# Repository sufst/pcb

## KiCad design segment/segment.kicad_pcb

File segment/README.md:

# Segment PCB Info

To comply with isolation requirements for HV and LV, this design has been split
up into two PCBs. The "HV" board provides the fusing and connections for the
voltage taps. The "LV" board provides the connections to the thermistors and
merges their grounds. The boards are designed to be stacked vertically with
the LV board on top of the HV board. The boards should be connected via an 
insulating material and should be separated either by at least 30mm of air
or be separated by a barrier of moisture resistant, insulating material.

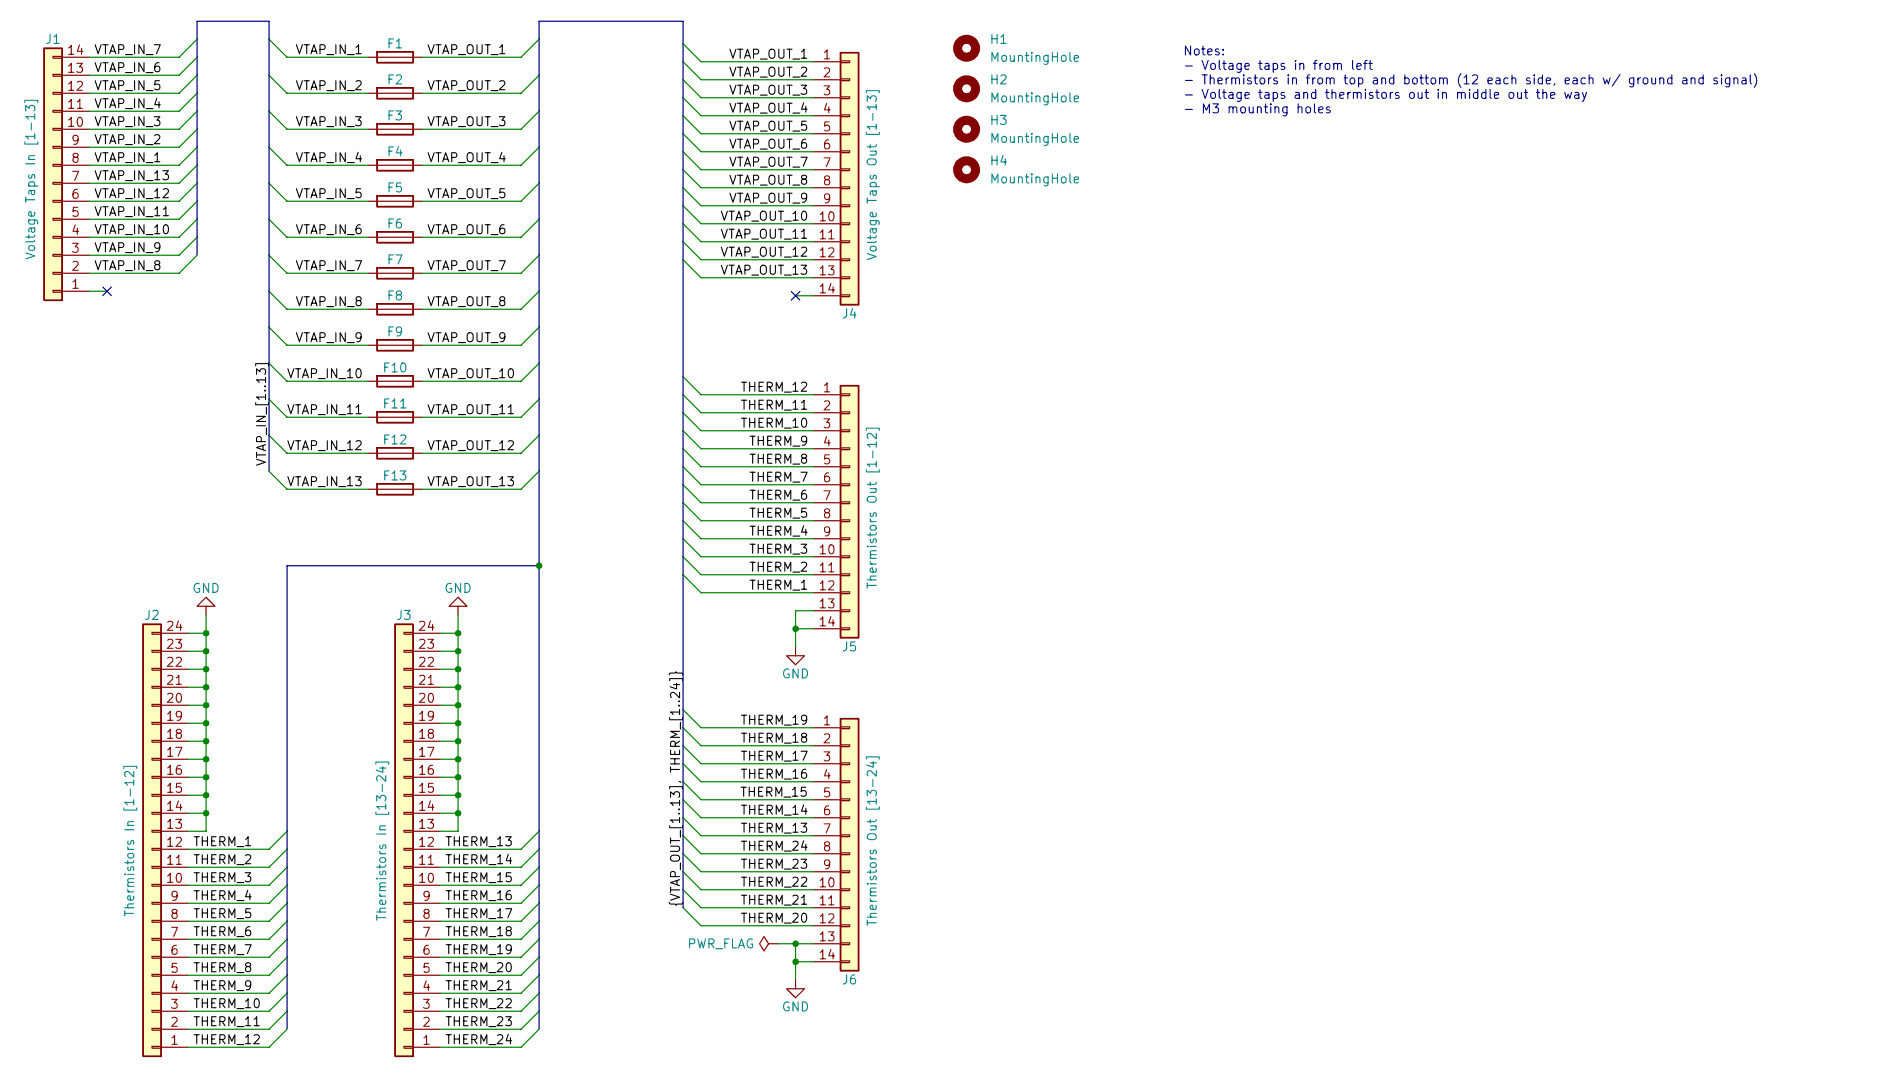
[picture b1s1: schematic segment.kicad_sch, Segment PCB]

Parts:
F1, F2, F3, F4, F5, F6, F7, F8, F9, F10, F11, F12, F13: Fuse; Littelfuse-04611-25ER
H1, H2, H3, H4: MountingHole; MountingHole_4.3mm_M4
J1: Voltage Taps In [1-13]; Molex_Micro-Fit_3.0_43045-1400_2x07_P3.00mm_Horizontal
J2: Thermistors In [1-12]; Molex_Micro-Fit_3.0_43045-2400_2x12_P3.00mm_Horizontal
J3: Thermistors In [13-24]; Molex_Micro-Fit_3.0_43045-2400_2x12_P3.00mm_Horizontal
J4: Voltage Taps Out [1-13]; Molex_Micro-Fit_3.0_43045-1412_2x07_P3.00mm_Vertical
J5: Thermistors Out [1-12]; Molex_Micro-Fit_3.0_43045-1412_2x07_P3.00mm_Vertical
J6: Thermistors Out [13-24]; Molex_Micro-Fit_3.0_43045-1412_2x07_P3.00mm_Vertical

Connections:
/THERM_1: J2.12, J5.12
/THERM_2: J2.11, J5.11
/THERM_3: J2.10, J5.10
/THERM_4: J2.9, J5.9
/THERM_5: J2.8, J5.8
/THERM_6: J2.7, J5.7
/THERM_7: J2.6, J5.6
/THERM_8: J2.5, J5.5
/THERM_9: J2.4, J5.4
/THERM_10: J2.3, J5.3
/THERM_11: J2.2, J5.2
/THERM_12: J2.1, J5.1
/THERM_13: J3.12, J6.7
/THERM_14: J3.11, J6.6
/THERM_15: J3.10, J6.5
/THERM_16: J3.9, J6.4
/THERM_17: J3.8, J6.3
/THERM_18: J3.7, J6.2
/THERM_19: J3.6, J6.1
/THERM_20: J3.5, J6.12
/THERM_21: J3.4, J6.11
/THERM_22: J3.3, J6.10
/THERM_23: J3.2, J6.9
/THERM_24: J3.1, J6.8
/VTAP_IN_1: F1.2, J1.8
/VTAP_IN_2: F2.2, J1.9
/VTAP_IN_3: F3.2, J1.10
/VTAP_IN_4: F4.2, J1.11
/VTAP_IN_5: F5.2, J1.12
/VTAP_IN_6: F6.2, J1.13
/VTAP_IN_7: F7.2, J1.14
/VTAP_IN_8: F8.2, J1.2
/VTAP_IN_9: F9.2, J1.3
/VTAP_IN_10: F10.2, J1.4
/VTAP_IN_11: F11.2, J1.5
/VTAP_IN_12: F12.2, J1.6
/VTAP_IN_13: F13.2, J1.7
/VTAP_OUT_1: F1.1, J4.1
/VTAP_OUT_2: F2.1, J4.2
/VTAP_OUT_3: F3.1, J4.3
/VTAP_OUT_4: F4.1, J4.4
/VTAP_OUT_5: F5.1, J4.5
/VTAP_OUT_6: F6.1, J4.6
/VTAP_OUT_7: F7.1, J4.7
/VTAP_OUT_8: F8.1, J4.8
/VTAP_OUT_9: F9.1, J4.9
/VTAP_OUT_10: F10.1, J4.10
/VTAP_OUT_11: F11.1, J4.11
/VTAP_OUT_12: F12.1, J4.12
/VTAP_OUT_13: F13.1, J4.13
GND: J2.13, J2.14, J2.15, J2.16, J2.17, J2.18, J2.19, J2.20, J2.21, J2.22, J2.23, J2.24, J3.13, J3.14, J3.15, J3.16, J3.17, J3.18, J3.19, J3.20, J3.21, J3.22, J3.23, J3.24, J5.13, J5.14, J6.13, J6.14

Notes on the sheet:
Notes: - Voltage taps in from left - Thermistors in from top and bottom (12 each side, each w/ ground and signal) - Voltage taps and thermistors out in middle out the way - M3 mounting holes

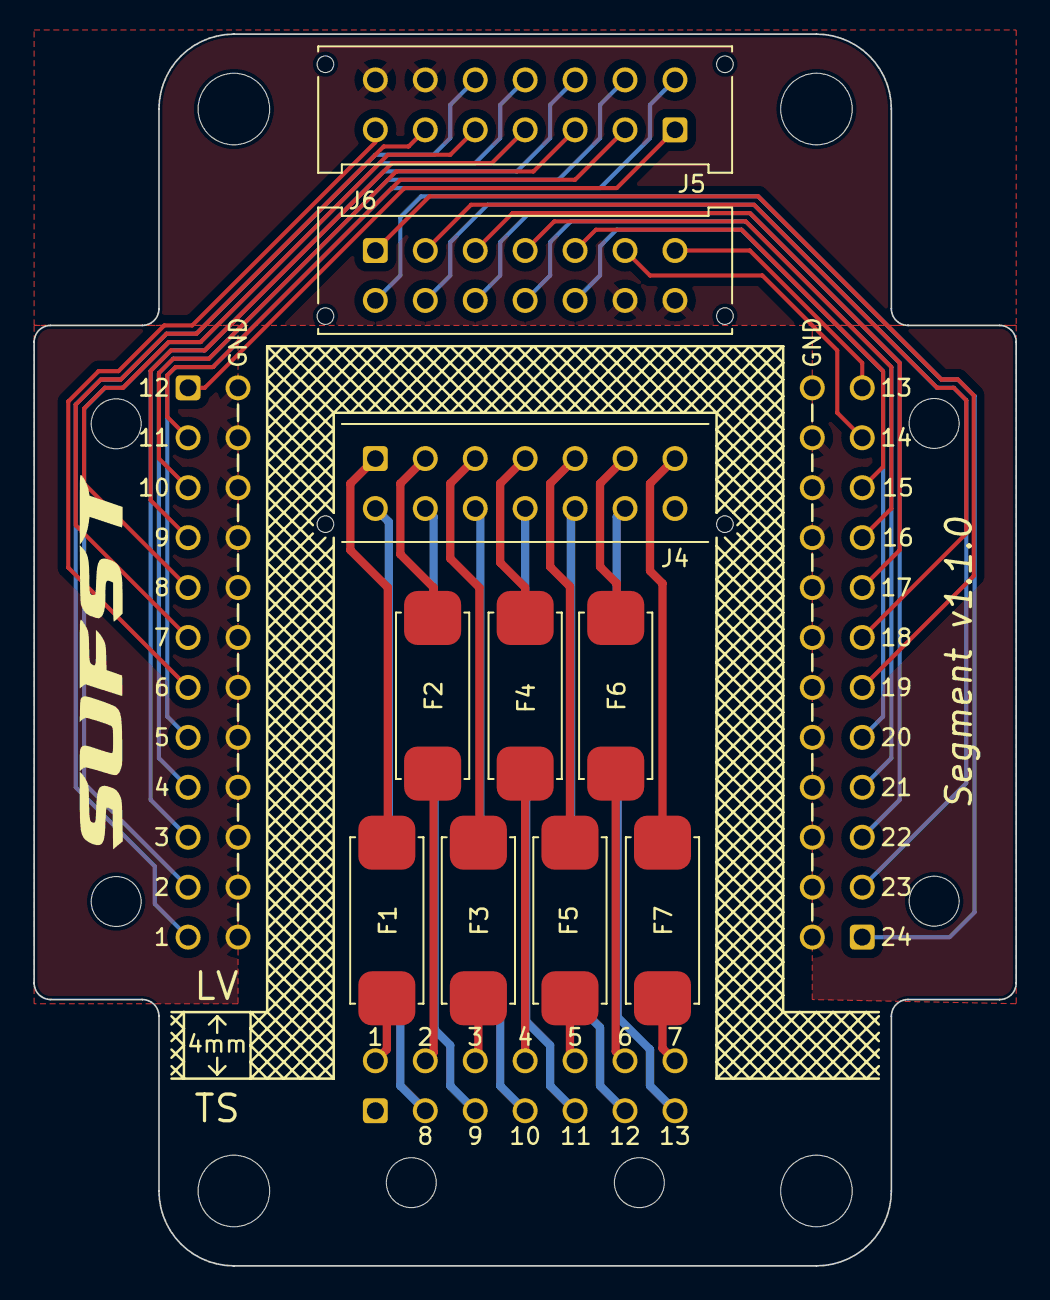
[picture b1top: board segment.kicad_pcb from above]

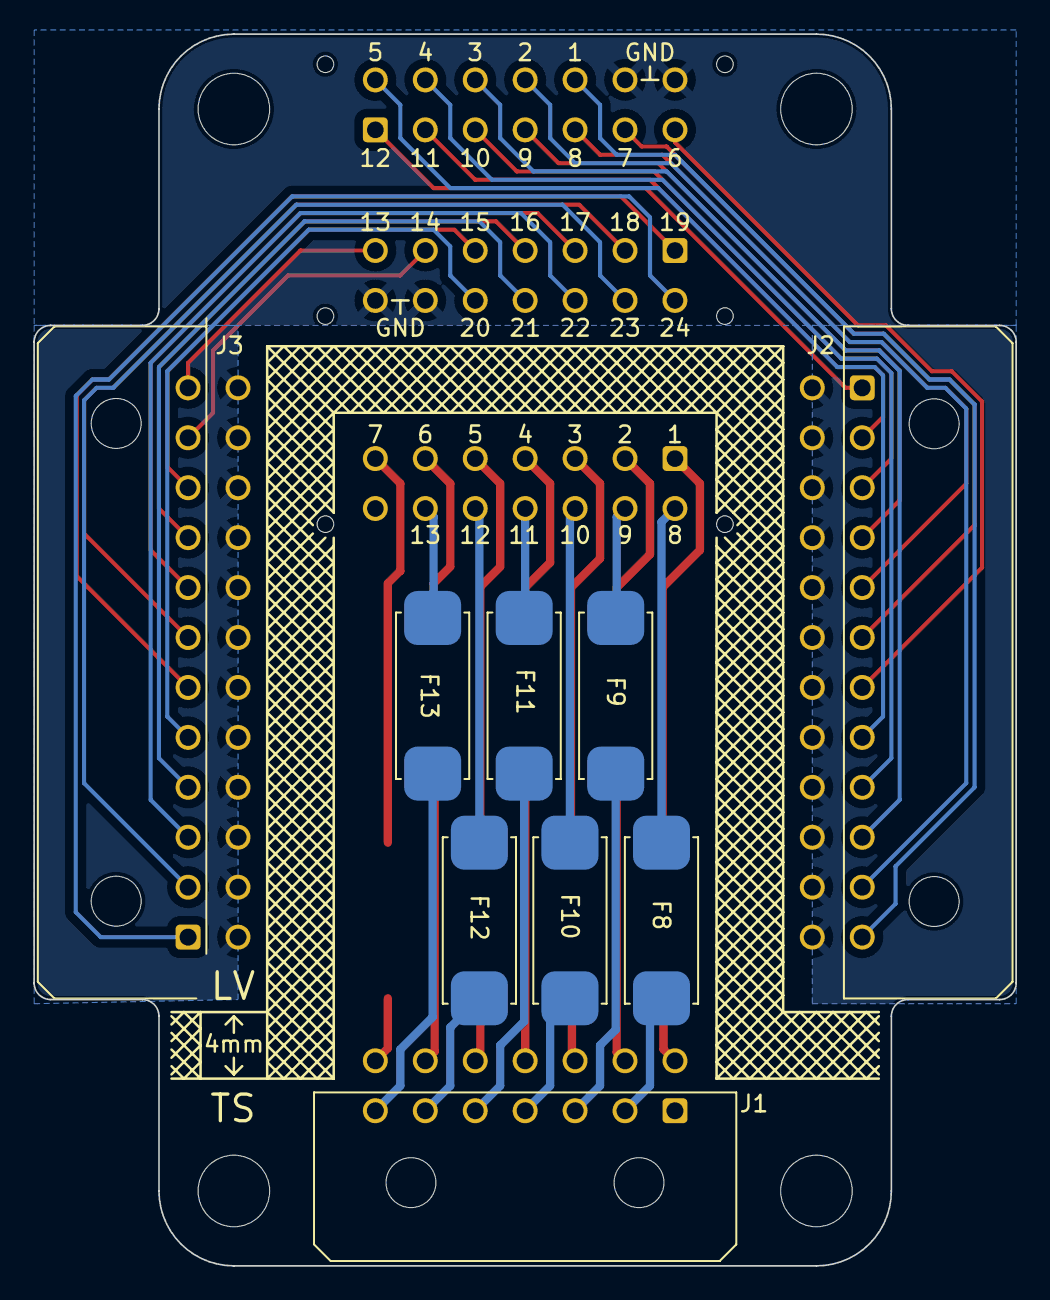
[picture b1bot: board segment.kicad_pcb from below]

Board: 4 copper layers, 59.0 x 74.0 mm, 23 parts (9 on the bottom side), 51 nets.

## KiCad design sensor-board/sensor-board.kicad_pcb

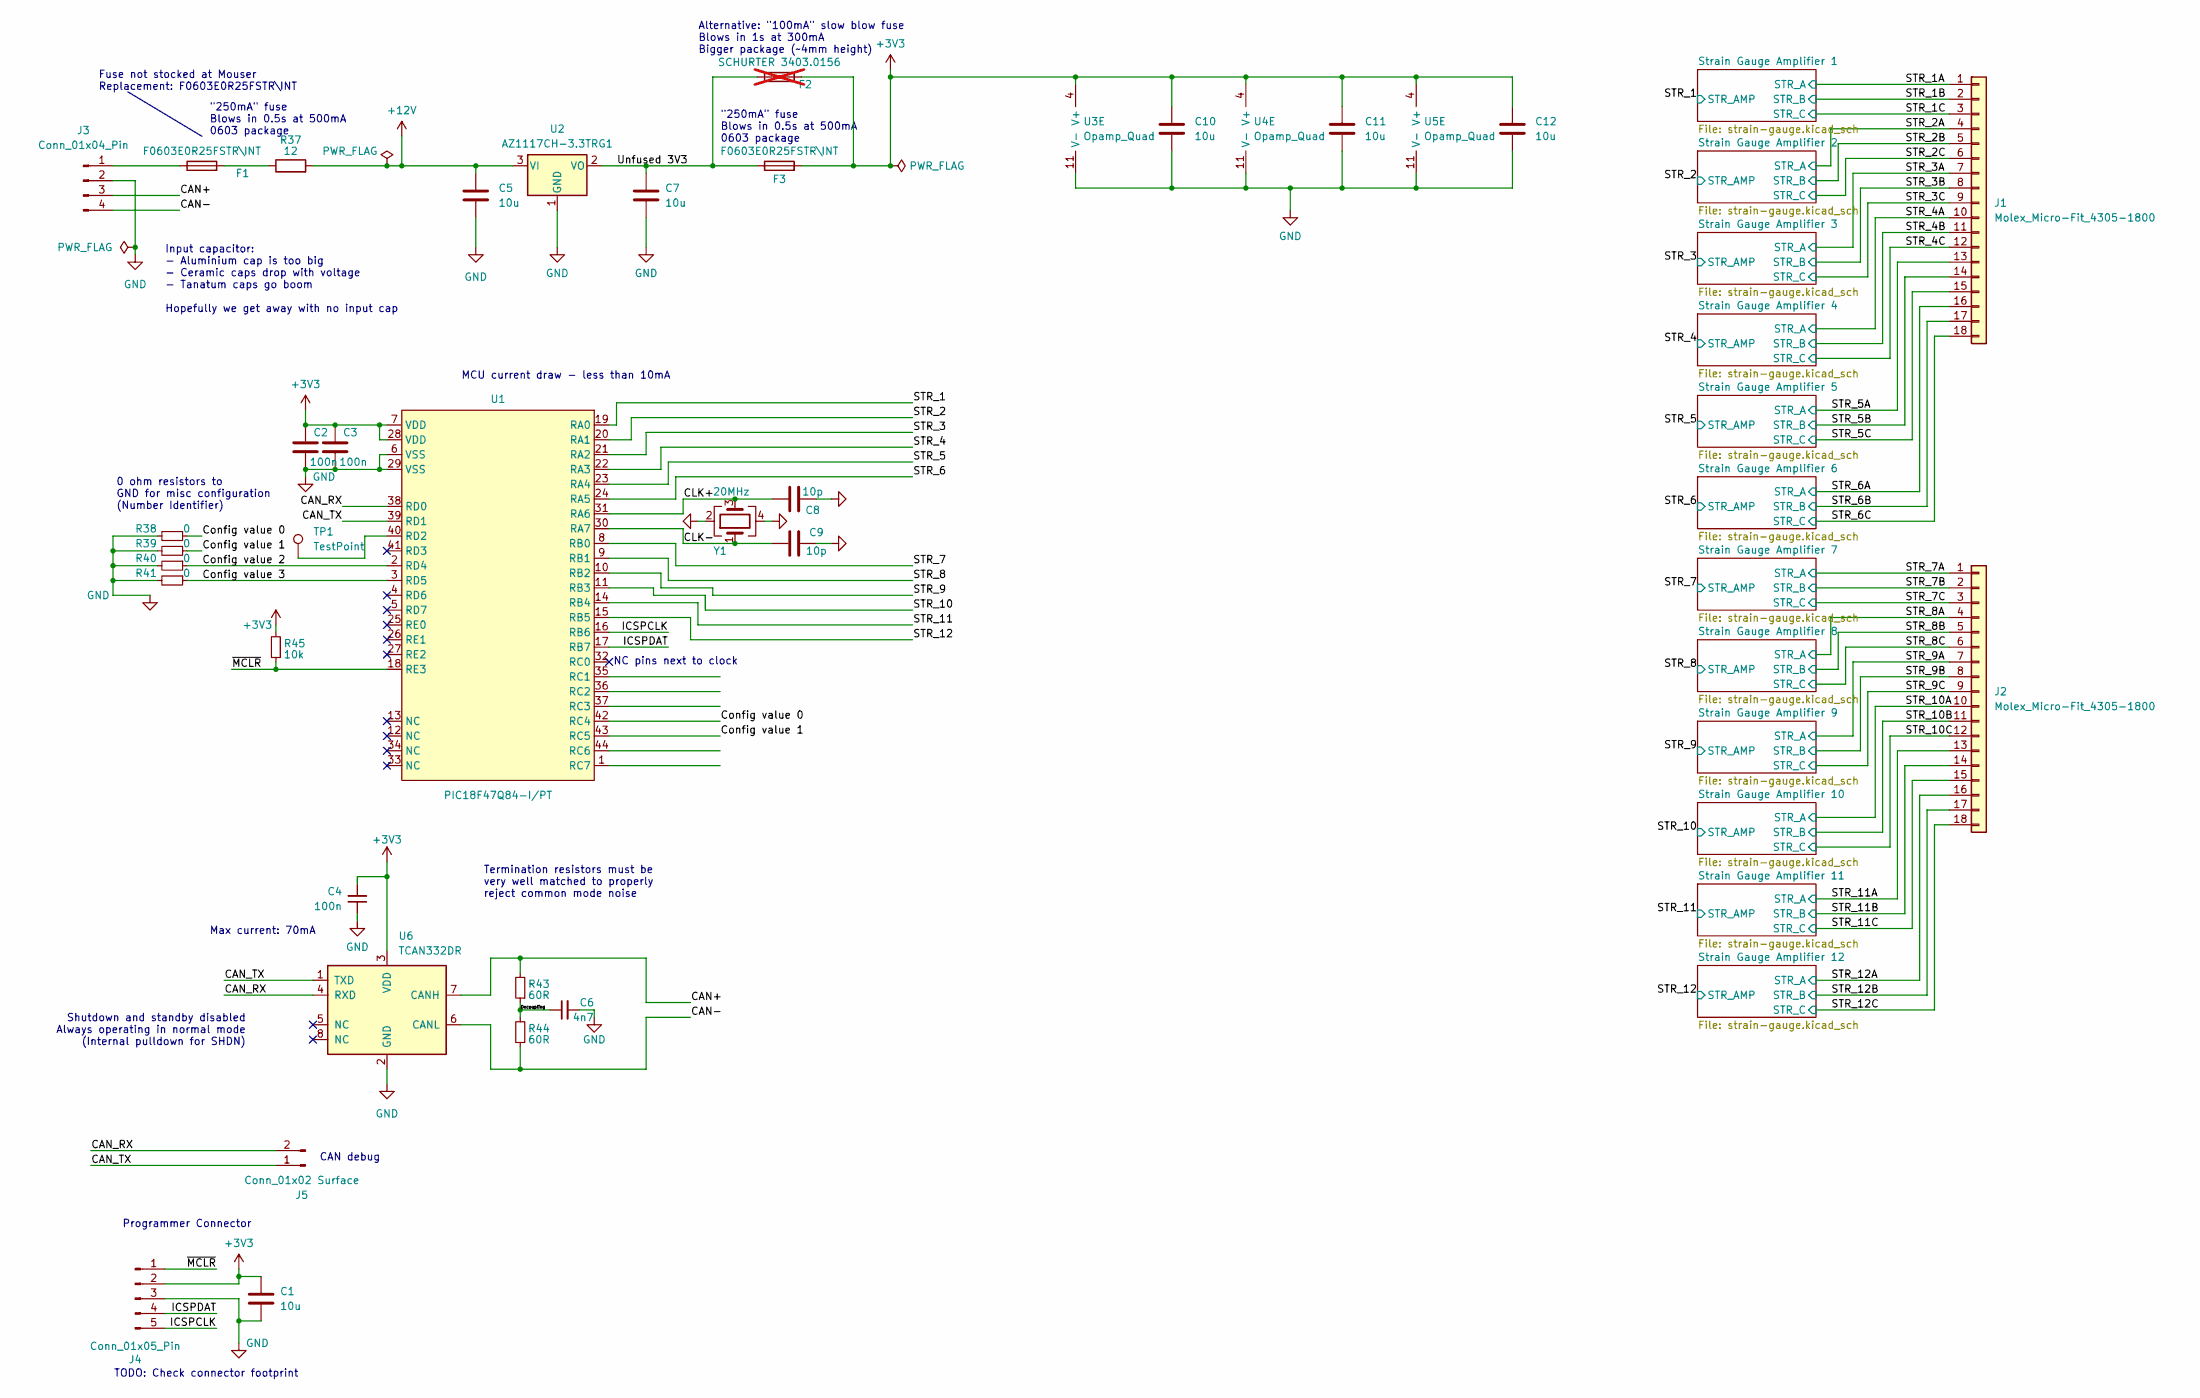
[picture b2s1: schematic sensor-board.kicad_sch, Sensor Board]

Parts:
C1, C5, C7, C10, C11, C12: 10u; C_0805_2012Metric_Pad1.18x1.45mm_HandSolder; Manufacturer_Part_Number GRT21BC71E106KE13L; Mouser Part Number 81-GRT21BC71E106KE13
C2, C3, C4: 100n; C_0805_2012Metric_Pad1.18x1.45mm_HandSolder; Manufacturer_Part_Number KAM21BR71H104JM; Mouser Part Number 581-KAM21BR71H104JM
C6: 4n7; C_0805_2012Metric_Pad1.18x1.45mm_HandSolder; Manufacturer_Part_Number KAM21BR71H472KM; Mouser Part Number 581-KAM21BR71H472KM
C8, C9: 10p; C_0603_1608Metric_Pad1.08x0.95mm_HandSolder; Manufacturer_Part_Number C0805C100J1RACAUTO; Mouser Part Number 80-C0805C100J1RAUTO
F1, F3: F0603E0R25FSTR\INT; Fuse_0603_1608Metric_Pad1.05x0.95mm_HandSolder; Manufacturer_Part_Number F0603E0R25FSTR\INT; Mouser Part Number 581-F0603E0R25FSTRIN
F2: SCHURTER 3403.0156; Fuse_Schurter_UMT250; not fitted
J1, J2: Molex_Micro-Fit_4305-1800; Molex_Micro-Fit_3.0_43045-1800_2x09_P3.00mm_Horizontal
J3: Conn_01x04_Pin; Molex_Micro-Fit_3.0_43650-0400_1x04_P3.00mm_Horizontal; Manufacturer_Part_Number 43650-0400; Mouser Part Number 538-43650-0400
J4: Conn_01x05_Pin; Conn5_SMD; Manufacturer_Part_Number 5-146282-5; Mouser Part Number 571-5-146282-5
J5: Conn_01x02 Surface; Conn2_SMD
R37: 12; R_0805_2012Metric_Pad1.20x1.40mm_HandSolder; Manufacturer_Part_Number CRCW080512R0FKEAHP; Mouser Part Number 71-CRCW080512R0FKEAH
R38, R39, R40, R41: 0; R_0805_2012Metric_Pad1.20x1.40mm_HandSolder; Manufacturer_Part_Number CR0805AJ/-000EAS; Mouser Part Number 652-CR0805AJ/-000EAS
R43, R44: 60R; R_0805_2012Metric_Pad1.20x1.40mm_HandSolder; Manufacturer_Part_Number ERJ-P06D60R4V; Mouser Part Number 667-ERJ-P06D60R4V
R45: 10k; R_0805_2012Metric_Pad1.20x1.40mm_HandSolder; Manufacturer_Part_Number CRGH0805F12R; Mouser Part Number 279-CRGH0805F12R
TP1: TestPoint; TestPoint_Keystone_5010-5014_Multipurpose
U1: PIC18F47Q84-I/PT; TQFP-44_10x10mm_P0.8mm; Manufacturer_Part_Number PIC18F47Q84-I/PT; Mouser Part Number 579-PIC18F47Q84-I/PT
U2: AZ1117CH-3.3TRG1; SOT-223-3_TabPin2; Manufacturer_Part_Number AZ1117CH-3.3TRG1; Mouser Part Number 621-AZ1117CH-3.3TRG1
U3, U4, U5: Opamp_Quad
U6: TCAN332DR; SOIC-8_3.9x4.9mm_P1.27mm; Manufacturer_Part_Number TCAN332DR; Mouser Part Number 700-MAX3051ESA
Y1: 20MHz; Crystal_SMD_SeikoEpson_FA128-4Pin_2.0x1.6mm; Manufacturer_Part_Number FA-128 20.00M-A0AAYYG80RE0; Mouser Part Number 732-FA12820A0AAYYG80

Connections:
/CAN+: J3.3, R43.2, U6.7 (CANH)
/CAN-: J3.4, R44.1, U6.6 (CANL)
/CAN_RX: J5.2, U1.38 (RD0), U6.4 (RXD)
/CAN_TX: J5.1, U1.39 (RD1), U6.1 (TXD)
/CLK+: C8.1, U1.31 (RA6), Y1.3
/CLK-: C9.1, U1.30 (RA7), Y1.1
/Config value 0: R38.1, U1.42 (RC4)
/Config value 1: R39.1, U1.43 (RC5)
/Config value 2: R40.1, U1.2 (RD4)
/Config value 3: R41.1, U1.3 (RD5)
/Decoupling: C6.1, R43.1, R44.2
/ICSPCLK: J4.5, U1.16 (RB6)
/ICSPDAT: J4.4, U1.17 (RB7)
/STR_1: U1.19 (RA0), U3.1
/STR_1A: J1.1, U3.3 (+); also elsewhere on the board
/STR_1B: J1.2; also elsewhere on the board
/STR_2: U1.20 (RA1); also elsewhere on the board
/STR_2A: J1.4; also elsewhere on the board
/STR_2B: J1.5; also elsewhere on the board
/STR_3: U1.21 (RA2), U3.8
/STR_3A: J1.7, U3.10 (+); also elsewhere on the board
/STR_3B: J1.8; also elsewhere on the board
/STR_4: U1.22 (RA3), U3.14
/STR_4A: J1.10, U3.12 (+); also elsewhere on the board
/STR_4B: J1.11; also elsewhere on the board
/STR_5: U1.23 (RA4), U4.1
/STR_5A: J1.13, U4.3 (+); also elsewhere on the board
/STR_5B: J1.14; also elsewhere on the board
/STR_6: U1.24 (RA5); also elsewhere on the board
/STR_6A: J1.16; also elsewhere on the board
/STR_6B: J1.17; also elsewhere on the board
/STR_7: U1.8 (RB0), U4.8
/STR_7A: J2.1, U4.10 (+); also elsewhere on the board
/STR_7B: J2.2; also elsewhere on the board
/STR_8: U1.9 (RB1), U4.14
/STR_8A: J2.4, U4.12 (+); also elsewhere on the board
/STR_8B: J2.5; also elsewhere on the board
/STR_9: U1.10 (RB2), U5.1
/STR_9A: J2.7, U5.3 (+); also elsewhere on the board
/STR_9B: J2.8; also elsewhere on the board
/STR_10: U1.11 (RB3); also elsewhere on the board
/STR_10A: J2.10; also elsewhere on the board
/STR_10B: J2.11; also elsewhere on the board
/STR_11: U1.14 (RB4), U5.8
/STR_11A: J2.13, U5.10 (+); also elsewhere on the board
/STR_11B: J2.14; also elsewhere on the board
/STR_12: U1.15 (RB5), U5.14
/STR_12A: J2.16, U5.12 (+); also elsewhere on the board
/STR_12B: J2.17; also elsewhere on the board
/Unfused 3V3: C7.1, F2.1, F3.1, U2.2 (VO)
/~MCLR: J4.1, R45.1, U1.18 (RE3)
GND: C1.2, C2.2, C3.2, C4.1, C5.2, C6.2, C7.2, C8.2, C9.2, C10.2, C11.2, C12.2, J1.3, J1.6, J1.9, J1.12, J1.15, J1.18, J2.3, J2.6, J2.9, J2.12, J2.15, J2.18, J3.2, J4.3, R38.2, R39.2, R40.2, R41.2, U1.6 (VSS), U1.29 (VSS), U2.1 (GND), U3.11 (V-), U4.11 (V-), U5.11 (V-), U6.2 (GND), Y1.2, Y1.4; also elsewhere on the board
unnamed: F1.2, R37.1
unnamed: F1.1, J3.1
unnamed: TP1.1, U1.40 (RD2)
unnamed 55: U3.2 (-); also elsewhere on the board
unnamed 57: U3.9 (-); also elsewhere on the board
unnamed 58: U3.13 (-); also elsewhere on the board
unnamed 59: U4.2 (-); also elsewhere on the board
unnamed 61: U4.9 (-); also elsewhere on the board
unnamed 62: U4.13 (-); also elsewhere on the board
unnamed 63: U5.2 (-); also elsewhere on the board
unnamed 65: U5.9 (-); also elsewhere on the board
unnamed 66: U5.13 (-); also elsewhere on the board

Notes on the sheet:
0 ohm resistors to GND for misc configuration (Number Identifier)
Shutdown and standby disabled Always operating in normal mode (Internal pulldown for SHDN)
NC pins next to clock
"250mA" fuse Blows in 0.5s at 500mA 0603 package
MCU current draw - less than 10mA
Input capacitor: - Aluminium cap is too big - Ceramic caps drop with voltage - Tanatum caps go boom Hopefully we get away with no input cap
CAN debug
Alternative: "100mA" slow blow fuse Blows in 1s at 300mA Bigger package (~4mm height)
Max current: 70mA
TODO: Check connector footprint
Fuse not stocked at Mouser Replacement: F0603E0R25FSTR\INT
Programmer Connector
Termination resistors must be very well matched to properly reject common mode noise

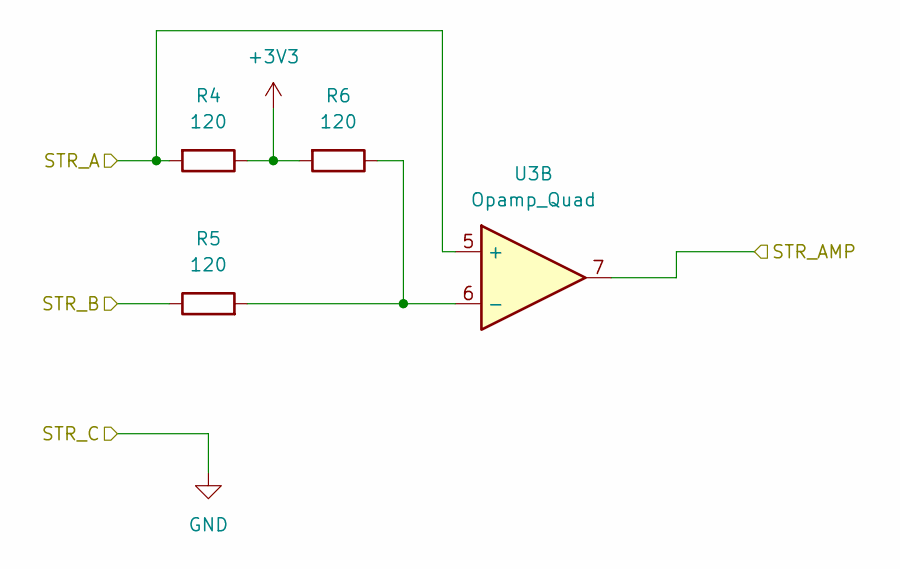
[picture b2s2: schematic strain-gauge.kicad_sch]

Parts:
R4, R5, R6: 120; R_0805_2012Metric
U3: Opamp_Quad; SO-14_3.9x8.65mm_P1.27mm

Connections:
/STR_1: U3.1; also elsewhere on the board
/STR_1A: U3.3 (+); also elsewhere on the board
/STR_2: U3.7; also elsewhere on the board
/STR_2A: R4.2, U3.5 (+); also elsewhere on the board
/STR_2B: R5.1; also elsewhere on the board
/STR_3: U3.8; also elsewhere on the board
/STR_3A: U3.10 (+); also elsewhere on the board
/STR_4: U3.14; also elsewhere on the board
/STR_4A: U3.12 (+); also elsewhere on the board
unnamed 55: U3.2 (-); also elsewhere on the board
unnamed: R5.2, R6.1, U3.6 (-)
unnamed 57: U3.9 (-); also elsewhere on the board
unnamed 58: U3.13 (-); also elsewhere on the board

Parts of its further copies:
R1, R2, R3, R7, R8, R9, R10, R11, R12, R13, R14, R15, R16, R17, R18, R19, R20, R21, R22, R23, R24, R25, R26, R27, R28, R29, R30, R31, R32, R33, R34, R35, R36: 120; R_0805_2012Metric

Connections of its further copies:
/STR_1A: R1.2; also elsewhere on the board
/STR_1B: R2.1; also elsewhere on the board
/STR_3A: R7.2; also elsewhere on the board
/STR_3B: R8.1; also elsewhere on the board
/STR_4A: R10.2; also elsewhere on the board
/STR_4B: R11.1; also elsewhere on the board
/STR_5A: R13.2; also elsewhere on the board
/STR_5B: R14.1; also elsewhere on the board
/STR_6A: R16.2; also elsewhere on the board
/STR_6B: R17.1; also elsewhere on the board
/STR_7A: R19.2; also elsewhere on the board
/STR_7B: R20.1; also elsewhere on the board
/STR_8A: R22.2; also elsewhere on the board
/STR_8B: R23.1; also elsewhere on the board
/STR_9A: R25.2; also elsewhere on the board
/STR_9B: R26.1; also elsewhere on the board
/STR_10A: R28.2; also elsewhere on the board
/STR_10B: R29.1; also elsewhere on the board
/STR_11A: R31.2; also elsewhere on the board
/STR_11B: R32.1; also elsewhere on the board
/STR_12A: R34.2; also elsewhere on the board
/STR_12B: R35.1; also elsewhere on the board
unnamed 55: R2.2, R3.1; also elsewhere on the board
unnamed 57: R8.2, R9.1; also elsewhere on the board
unnamed 58: R11.2, R12.1; also elsewhere on the board
unnamed 59: R14.2, R15.1; also elsewhere on the board
unnamed 60: R17.2, R18.1; also elsewhere on the board
unnamed 61: R20.2, R21.1; also elsewhere on the board
unnamed 62: R23.2, R24.1; also elsewhere on the board
unnamed 63: R26.2, R27.1; also elsewhere on the board
unnamed 64: R29.2, R30.1; also elsewhere on the board
unnamed 65: R32.2, R33.1; also elsewhere on the board
unnamed 66: R35.2, R36.1; also elsewhere on the board

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
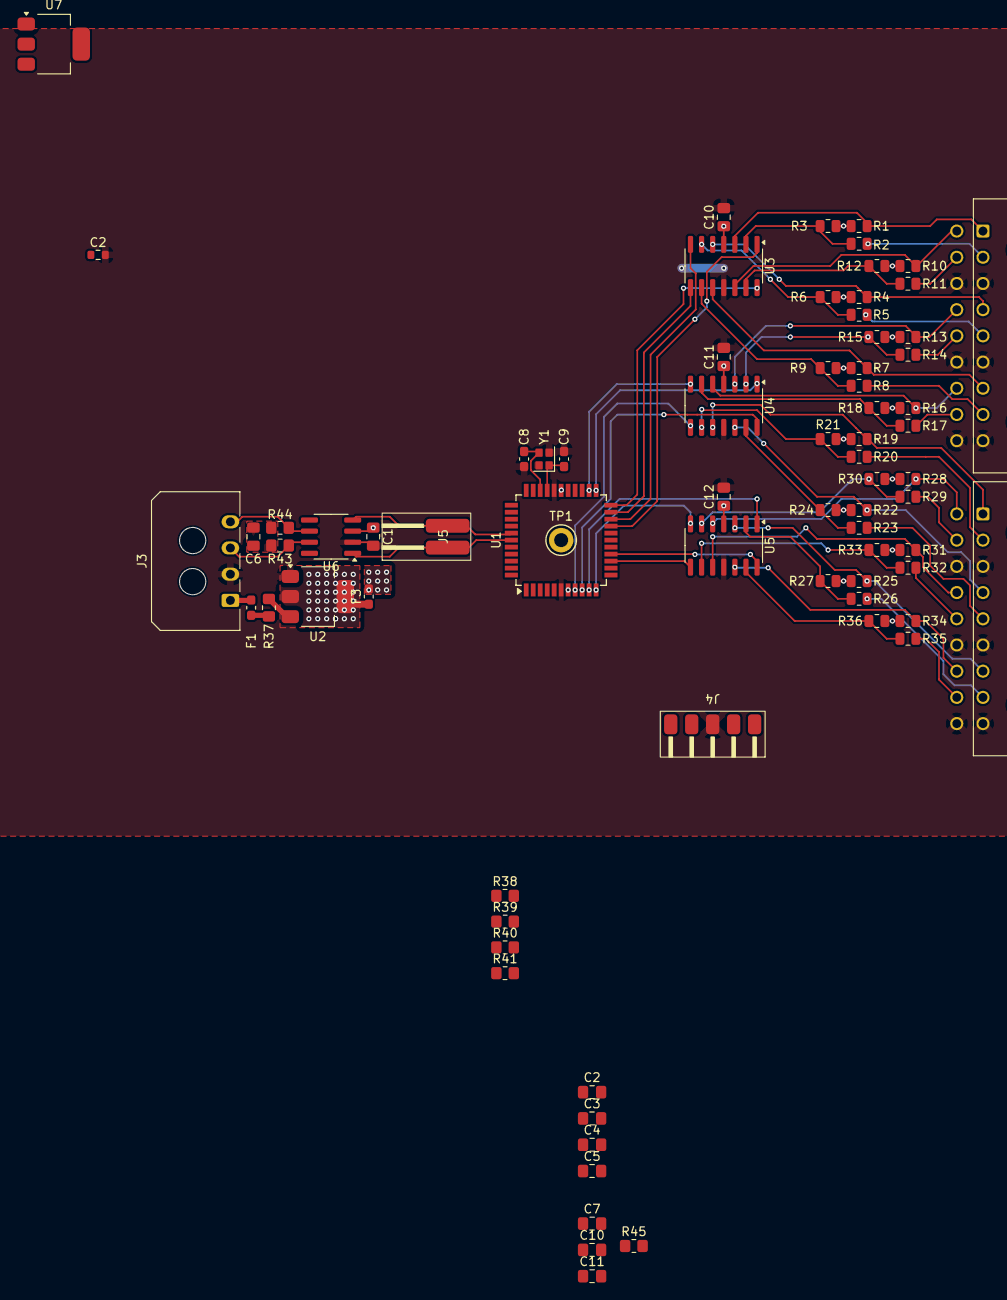
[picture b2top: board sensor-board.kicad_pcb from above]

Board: 2 copper layers, 75 parts (0 on the bottom side), 70 nets.

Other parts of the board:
C2#2: 100n; C_0805_2012Metric_Pad1.18x1.45mm_HandSolder
C10#2, C11#2: 10u; C_0805_2012Metric_Pad1.18x1.45mm_HandSolder
U7: AZ1117-5.0; SOT-223-3_TabPin2

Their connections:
GND: C2#2.2, C10#2.2, C11#2.2, U7.1 (GND); also elsewhere on the board

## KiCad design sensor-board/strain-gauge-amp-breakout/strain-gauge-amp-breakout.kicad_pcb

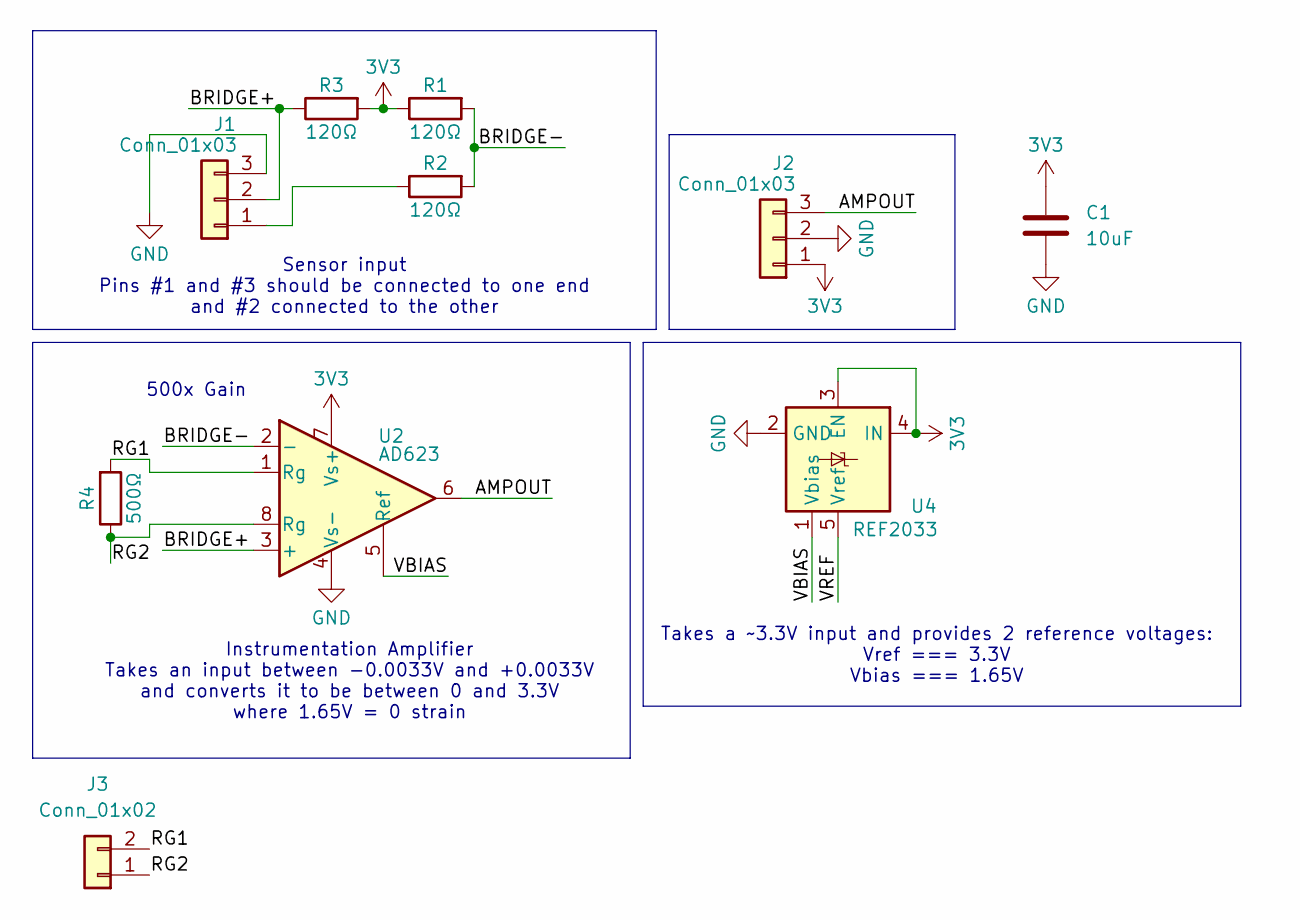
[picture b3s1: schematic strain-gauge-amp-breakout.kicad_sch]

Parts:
C1: 10uF; C_0805_2012Metric
J1, J2: Conn_01x03; PinHeader_1x03_P2.54mm_Vertical
J3: Conn_01x02; PinHeader_1x02_P2.54mm_Vertical
R1, R2, R3: 120Ω; R_0805_2012Metric
R4: 500Ω; R_0805_2012Metric
U2: AD623; MSOP-8-1EP_3x3mm_P0.65mm_EP1.5x1.8mm
U4: REF2033; SOT-23-5

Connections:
3V3: C1.1, J2.1, R1.1, R3.2, U2.7 (Vs+), U4.3 (EN), U4.4 (IN)
/AMPOUT: J2.3, U2.6
/BRIDGE+: J1.2, R3.1, U2.3 (+)
/BRIDGE-: R1.2, R2.2, U2.2 (-)
/RG1: J3.2, R4.2, U2.1 (Rg)
/RG2: J3.1, R4.1, U2.8 (Rg)
/VBIAS: U2.5 (Ref), U4.1 (Vbias)
/VREF: U4.5 (Vref)
GND: C1.2, J1.3, J2.2, U2.4 (Vs-), U4.2 (GND)
unnamed: J1.1, R2.1

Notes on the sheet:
Instrumentation Amplifier Takes an input between -0.0033V and +0.0033V and converts it to be between 0 and 3.3V where 1.65V = 0 strain
Sensor input Pins #1 and #3 should be connected to one end and #2 connected to the other
Takes a ~3.3V input and provides 2 reference voltages: Vref === 3.3V Vbias === 1.65V
500x Gain

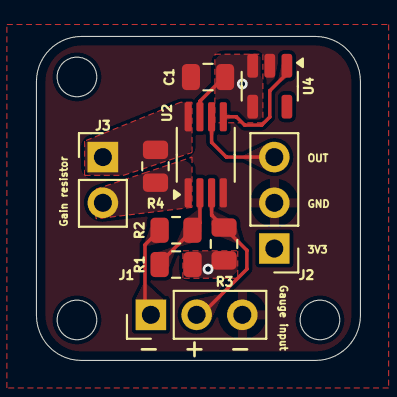
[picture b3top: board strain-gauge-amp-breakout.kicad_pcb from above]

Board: 2 copper layers, 18.0 x 18.0 mm, 13 parts (0 on the bottom side), 9 nets.

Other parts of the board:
H1, H2, H3: MountingHole; MountingHole_2.2mm_M2

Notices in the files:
parts and their libraries:
License: Apache-2.0
